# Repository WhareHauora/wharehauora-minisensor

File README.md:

# wharehauora-minisensor
Minisensor Schematic and PCB design files

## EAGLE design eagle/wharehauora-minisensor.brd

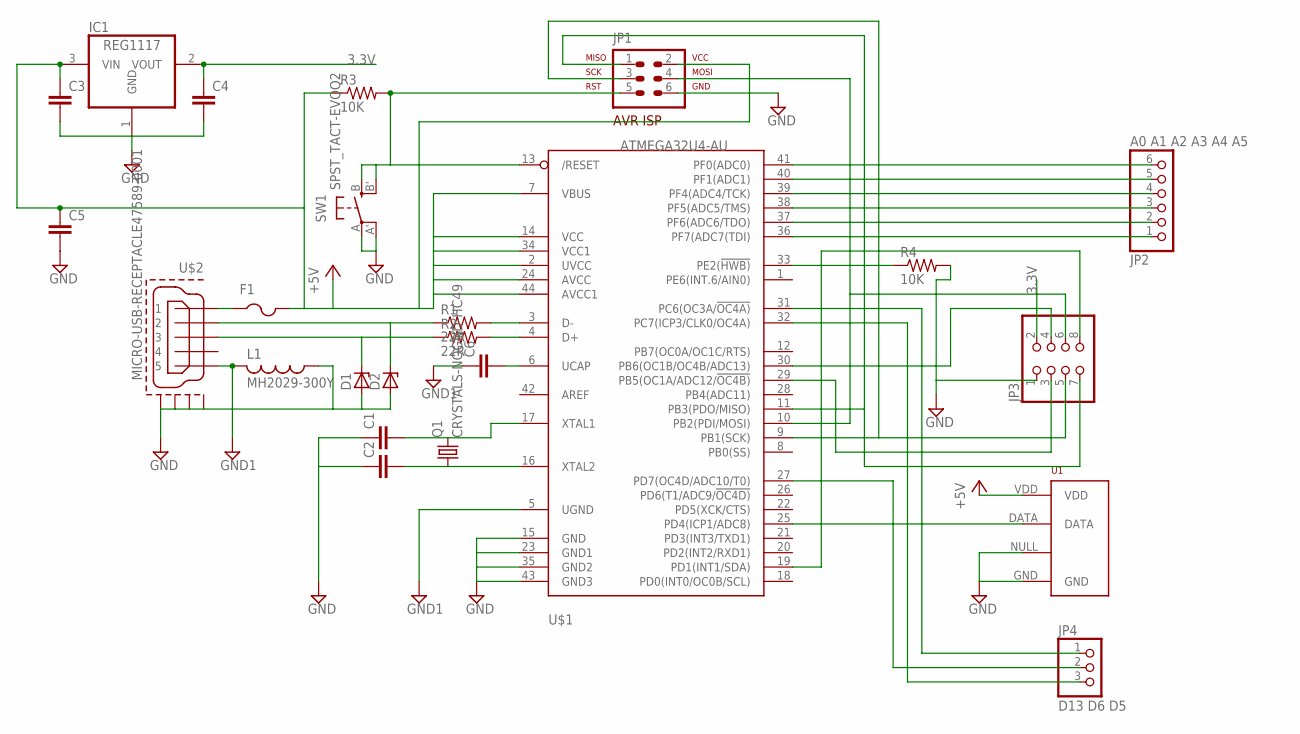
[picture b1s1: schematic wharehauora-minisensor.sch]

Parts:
C1, C2: CC0603; C0603
C3, C4, C6: C-EUC0805; C0805
C5: C-EUC0603; C0603
D1, D2: ZENER-DIODESOD80C; SOD80C
F1: PTCFUSE-1812; 1812
IC1: REG1117; SOT223
JP1: AVR-ISP-6VERT; AVR-ISP-6
JP2: A0 A1 A2 A3 A4 A5; 1X06
JP3: PINHD-2X4; 2X04
JP4: D13 D6 D5; 1X03
L1: MH2029-300Y; L2012C
Q1: CRYSTALS-NOGND-HC49; HC49
R1, R2: 22R; R0603
R3, R4: 10K; R0603
SW1: SPST_TACT-EVQQ2; EVQ-Q2
U1: RHT03_DHT-22_AM2302RA; RHT03_DHT-22/RA
U$1: ATMEGA32U4-AU; TQFP44
U$2: MICRO-USB-RECEPTACLE47589-0001; 47589-0001

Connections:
3.3V: C4.1, IC1.2 (VOUT), JP3.2
+5V: C3.1, C5.1, F1.2, IC1.3 (VIN), JP1.2, R3.1, U1.VDD, U$1.2 (UVCC), U$1.7 (VBUS), U$1.14 (VCC), U$1.24 (AVCC), U$1.34 (VCC1), U$1.44 (AVCC1)
GND: C1.1, C2.1, C3.2, C4.2, C5.2, D1.A, D2.A, IC1.1 (GND), JP1.6, JP3.1, L1.1, R4.2, SW1.A, SW1.A' (P1), U1.GND, U1.NULL, U$1.15 (GND), U$1.23 (GND1), U$1.35 (GND2), U$1.43 (GND3), U$2.CASING1 (GND1), U$2.CASING2 (GND2), U$2.CASING3 (GND3), U$2.CASING4 (GND4)
GND1: C6.1, L1.2, U$1.5 (UGND), U$2.5
unnamed: R1.2, U$1.3 (D-)
unnamed: R2.2, U$1.4 (D+)
unnamed: D1.C, R2.1, U$2.3
unnamed: D2.C, R1.1, U$2.2
unnamed: C1.2, Q1.2, U$1.17 (XTAL1)
unnamed: F1.1, U$2.1
unnamed: C2.2, Q1.1, U$1.16 (XTAL2)
unnamed: JP3.3, U$1.29 (PB5(OC1A/ADC12/!OC4B))
unnamed: JP3.4, U$1.30 (PB6(OC1B/OC4B/ADC13))
unnamed: JP1.5, R3.2, SW1.B (S), SW1.B' (S1), U$1.13 (/RESET)
unnamed: JP1.3, JP3.5, U$1.9 (PB1(SCK))
unnamed: JP1.1, JP3.7, U$1.11 (PB3(PDO/MISO))
unnamed: JP1.4, JP3.6, U$1.10 (PB2(PDI/MOSI))
unnamed: JP3.8, U$1.19 (PD1(INT1/SDA))
unnamed: JP2.1, U$1.36 (PF7(ADC7(TDI))
unnamed: JP2.2, U$1.37 (PF6(ADC6/TDO))
unnamed: JP2.3, U$1.38 (PF5(ADC5/TMS))
unnamed: JP2.4, U$1.39 (PF4(ADC4/TCK))
unnamed: JP2.5, U$1.40 (PF1(ADC1))
unnamed: JP2.6, U$1.41 (PF0(ADC0))
unnamed: U1.DATA, U$1.25 (PD4(ICP1/ADC8))
unnamed: C6.2, U$1.6 (UCAP)
unnamed: R4.1, U$1.33 (PE2(!HWB))
unnamed: JP4.2, U$1.27 (PD7(OC4D/ADC10/T0))
unnamed: JP4.1, U$1.31 (PC6(OC3A/!OC4A))
unnamed: JP4.3, U$1.32 (PC7(ICP3/CLK0/OC4A))

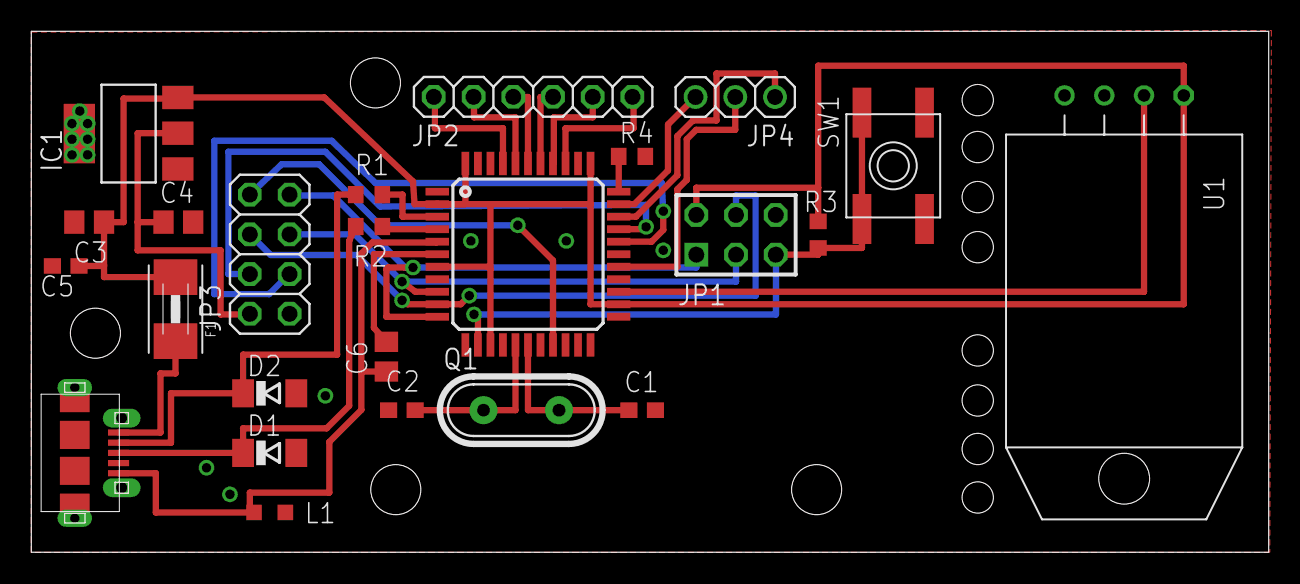
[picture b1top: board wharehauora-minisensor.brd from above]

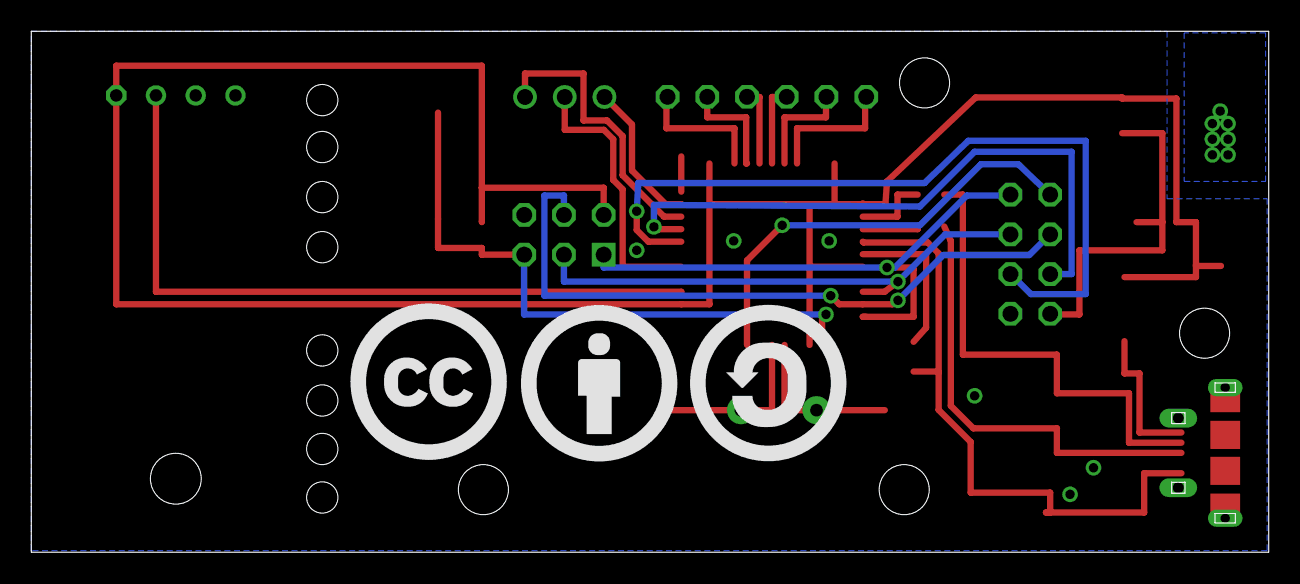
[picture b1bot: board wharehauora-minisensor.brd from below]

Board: 2 copper layers, 79.1 x 33.3 mm, 27 parts (3 on the bottom side), 30 nets.

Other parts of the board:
U$3: CC_TPLACE
U$4: BY_TPLACE
U$5: SA_TPLACE

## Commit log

2017-01-18 First commit of Eagle files - still needs work
2017-01-19 Adding in latest version
2017-01-20 Adding license. Updating PCB
2017-01-20 Latest board design
2017-01-20 Fix missing track

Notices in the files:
parts and their libraries:
con-molex-usb: (C) 2014 Tomasz Boleslaw CEDRO, cederom@tlen.pl, http://www.tomek.cedro.info.
